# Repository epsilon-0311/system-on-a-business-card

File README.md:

# The project has been moved to [Codeberg](https://codeberg.org/epsilon-0311/system-on-a-business-card). 

# system-on-a-business-card (SoBC)

The System on a Business Card is a miniature system in the size of a business card.
It is controlled by a ESP32-C3 microncontroller which shall run Zephyr RTOS in the future.
Since this goal is to also use the PCB is a business card, the predominant factor is the size which is 55x85 mm which seems to be the standard, at least for Europe.

A interactive Bill of Materials for the latest released board revision can be found [here](KiCAD/system-on-a-business-card/bom/ibom.html).
Alternatively, if you have the repositoy open on Github, please use this [link](https://htmlpreview.github.io/?https://github.com/epsilon-0311/system-on-a-business-card/blob/main/KiCAD/system-on-a-business-card/bom/ibom.html). 

For further details on how to customize the desing to add your contact details please have a look at [Customization of the PCB](KiCAD/doc/README.md#Customization-of-the-PCB).

## Hardware Design

The system uses the on-board USB Type C recepticle for power delivery and a ESP32-C3 as its host.
As the microcontroller also supports Bluetooth and Wifi the design includes a PCB antenna as well.
One of the most prominent elements of the board is 0.77 inch OLED screen which is used to display various graphics.
Instead of using typical low profile buttons the board has resistive touch pads for the main controls.
More details on the harware design can be found [here](KiCAD/doc/README.md).

Design renderings of a revision 1.A PCB:

Finished board revision 1.A PCB:

Fully assembled revision 1.A PCB:

## Zephyr
At the moment I'm working on getting Zephyr running.
A basic hardware configuration for the board is already available inside the Zephyr directory.
It builds and a minimal example is also available.
Unfortunately, I'm still waiting on my parts to finish the boards of my first batch.

As soon as I have a functioning board configuration, the goal is to submit the board to Zephry such that is officially supported.
Further, Zephyr currently does not support the used OLED dispaly controller (SSD1312).
Therefore, an additional goal is to submit a driver to the Zephyr project.

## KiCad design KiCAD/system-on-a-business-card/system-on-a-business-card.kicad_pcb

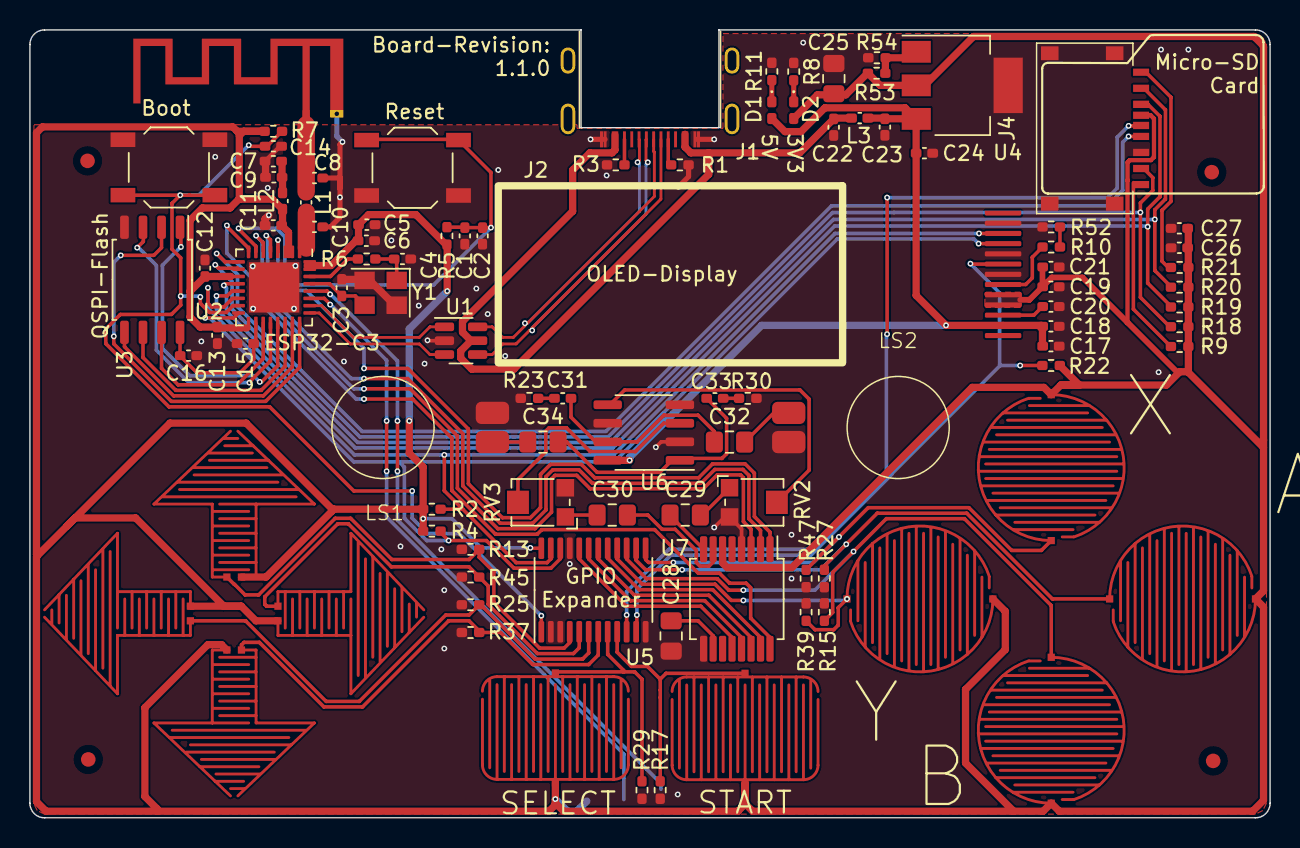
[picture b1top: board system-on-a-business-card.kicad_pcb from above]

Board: 2 copper layers, 85.0 x 54.0 mm, 103 parts (1 on the bottom side), 74 nets.

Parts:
AE1: Texas_SWRA117D_2.4GHz; Texas_SWRA117D_2.4GHz_Left
C1, C5: 1u; C_0402_1005Metric_Pad0.74x0.62mm_HandSolder
C2, C6, C9, C11, C12, C13, C14, C16, C17, C19, C22, C23, C27: 100n; C_0402_1005Metric_Pad0.74x0.62mm_HandSolder
C3, C4: 10p; C_0402_1005Metric_Pad0.74x0.62mm_HandSolder
C7, C15, C24, C26: 10u; C_0402_1005Metric_Pad0.74x0.62mm_HandSolder
C8, C10: 3p3; C_0402_1005Metric_Pad0.74x0.62mm_HandSolder
C18, C21: 4u7; C_0402_1005Metric_Pad0.74x0.62mm_HandSolder
C20: 2u2; C_0402_1005Metric_Pad0.74x0.62mm_HandSolder
C25, C28, C29, C30: 10u; C_0805_2012Metric_Pad1.18x1.45mm_HandSolder
C31, C33: 50n; C_0402_1005Metric_Pad0.74x0.62mm_HandSolder
C32, C34: 250u; C_0805_2012Metric_Pad1.18x1.45mm_HandSolder
D1, D2: XL-1005UGC; D_0402_1005Metric_Pad0.77x0.64mm_HandSolder
FID1, FID2, FID3, FID4: Fiducial; Fiducial_1mm_Mask2mm
J1: USB_C_Receptacle; USB_C_Receptacle_SHOU_HAN_TYPE_C_16P_CB1.6_073
J2: X077-6428TSWCG01-H13
J3: Conn_01x04_Socket; solder_pads_4x1
J4: TF-018B-H15; microSD_HC_Hanbo_Electronic_TF-018B-H15
L1, L2, L3: 2n2; L_0402_1005Metric_Pad0.77x0.64mm_HandSolder
LS1: Speaker_Left; Radial_10mm
LS2: Speaker_Right; Radial_10mm
R1, R2, R3, R4, R5, R7, R22: 5k1; R_0402_1005Metric_Pad0.72x0.64mm_HandSolder
R6, R53: 121R; R_0402_1005Metric_Pad0.72x0.64mm_HandSolder
R8, R9, R11, R18, R19, R20, R21: 47k; R_0402_1005Metric_Pad0.72x0.64mm_HandSolder
R10, R52: 200k; R_0402_1005Metric_Pad0.72x0.64mm_HandSolder
R12: BTN_UP; Resistive_Pad_Arrow_10mm
R13, R15, R17, R25, R27, R29, R37, R39, R45, R47: 1M; R_0402_1005Metric_Pad0.72x0.64mm_HandSolder
R14: BTN_B; Resistive_Pad_round_10_mm
R16: BTN_START; Resistive_Pad_rectangular_rounded_7x10mm
R23, R30: 10R; R_0402_1005Metric_Pad0.72x0.64mm_HandSolder
R24: BTN_LEFT; Resistive_Pad_Arrow_10mm
R26: BTN_A; Resistive_Pad_round_10_mm
R28: BTN_SELECT; Resistive_Pad_rectangular_rounded_7x10mm
R36: BTN_DOWN; Resistive_Pad_Arrow_10mm
R38: BTN_Y; Resistive_Pad_round_10_mm
R44: BTN_RIGHT; Resistive_Pad_Arrow_10mm
R46: BTN_X; Resistive_Pad_round_10_mm
R54: 75R; R_0402_1005Metric_Pad0.72x0.64mm_HandSolder
RV2, RV3: 10k; Potentiometer_Bourns_TC33X_Vertical
SW1, SW2: SW_Push; SW_SPST_TL3342
U1: USBLC6-2SC6; SOT-23-6
U2: ESP32-C3; QFN-32-1EP_5x5mm_P0.5mm_EP3.45x3.45mm
U3: ZD25WQ32C; SOP-8_5.28x5.23mm_P1.27mm
U4: ZD1117ILTRAD; SOT-223
U5: TCA9535PWR; TSSOP-24_4.4x7.8mm_P0.65mm
U6: RC4580; SOIC-8_3.9x4.9mm_P1.27mm
U7: PCM1754; SSOP-16_5.3x6.2mm_P0.65mm
Y1: 40MHz; Crystal_SMD_3225-4Pin_3.2x2.5mm

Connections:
+3.3V: C5.1, C6.1, C11.1, C12.1, C13.1, C19.1, C21.1, C25.1, C26.1, C27.1, D2.2 (A), J2.4, J2.5, J3.4, J4.4 (VDD), L2.2, R2.1, R4.1, R5.1, R7.1, R9.1, R12.2, R14.1, R16.2, R18.1, R19.1, R20.1, R21.1, R22.1, R24.2, R26.1, R28.2, R36.2, R38.1, R44.2, R46.1, R53.1, U2.2 (VDD3P3), U2.3 (VDD3P3), U2.11 (VDD3P3_RTC), U2.17 (VDD3P3_CPU), U2.31 (VDDA), U2.32 (VDDA), U4.2 (V_OUT), U5.24 (VCC), U7.6 (VCC)
+5V: C17.1, C18.1, C23.1, C24.1, D1.2 (A), J2.2, L3.2, U4.3 (V_IN), U6.8 (V+)
/Audio Circuit/BCLK: U2.4 (XTAL_32K_P/ADC1_CH0), U7.1 (BCK)
/Audio Circuit/DEMP: U5.19 (P16), U7.13 (DEMP)
/Audio Circuit/FMT: U5.17 (P14), U7.15 (FMT)
/Audio Circuit/LRCLK: U2.6 (GPIO2/ADC1_CH2), U7.3 (LRCK)
/Audio Circuit/MUTE: U5.18 (P15), U7.14 (MUTE)
/Audio Circuit/SCLK: U2.8 (GPIO3/ADC1_CH3), U7.16 (SCK)
/Audio Circuit/SERIAL_DATA: U2.5 (XTAL_32K_N/ADC1_CH1), U7.2 (DATA)
/Audio Circuit/TEST: U5.20 (P17), U7.12 (TEST)
/Display Circuit/SCL: J2.10, R4.2, U2.16 (GPIO10), U5.22 (SCL)
/Display Circuit/SDA: J2.11, R2.2, U2.14 (GPIO8), U5.23 (SDA)
/Host/MISO: J4.7 (DAT0), R18.2, U2.10 (MTDI/GPIO5/ADC2_CH0)
/Host/MOSI: J4.3 (CMD), R19.2, U2.13 (MTDO/GPIO7)
/Host/SCK: J4.5 (CLK), U2.9 (MTMS/GPIO4/ADC1_CH4)
/Host/SS: J4.2 (DAT3/CD), R20.2, U2.12 (MTCK/GPIO6)
/Power Circuit/USB_VBUS: C22.1, J1.A4 (VBUS), J1.A9 (VBUS), J1.B4 (VBUS), J1.B9 (VBUS), L3.1, U1.5 (VBUS)
/Resistive Touch Circuit/SDCard_DET: J4.9 (DET), U5.10 (P06)
A: R26.2, R27.1, U5.14 (P11)
B: R14.2, R15.1, U5.15 (P12)
BOOT: C14.1, R7.2, SW2.2, U2.15 (GPIO9/BOOT), U5.1 (~INT)
CC1: J1.A5 (CC1), R1.1
CC2: J1.B5 (CC2), R3.1
Channel_Left: C30.1, RV3.1
Channel_Right: C29.1, RV2.1
DOWN: R36.1, R37.1, U5.7 (P03)
GND: AE1.2 (GND), C1.2, C2.2, C3.1, C4.1, C5.2, C6.2, C7.2, C8.2, C9.2, C10.2, C11.2, C12.2, C13.2, C14.2, C15.2, C16.2, C17.2, C18.2, C19.2, C20.2, C21.2, C22.2, C23.2, C24.2, C25.2, C26.2, C27.2, C28.2, J1.A1 (GND), J1.A12 (GND), J1.B1 (GND), J1.B12 (GND), J2.7, J2.9, J2.12, J3.1, J4.6 (VSS), J4.10 (SHIELD), LS1.2, LS2.2, R1.2, R3.2, R8.2, R11.2, R13.2, R15.2, R17.2, R23.2, R25.2, R27.2, R29.2, R30.2, R37.2, R39.2, R45.2, R47.2, R52.1, R54.2, RV2.3, RV3.3, SW1.1, SW2.1, U1.2 (GND), U2.33 (GND), U3.4 (GND), U4.4 (GND), U5.2 (A1), U5.3 (A2), U5.12 (GND), U5.21 (A0), U6.2 (-), U6.4 (V-), U6.6 (-), U7.4 (DGND), U7.9 (AGND), Y1.2, Y1.4
LEFT: R24.1, R25.1, U5.6 (P02)
unnamed: AE1.1 (Feed), C8.1, L1.1
unnamed: C4.2, R6.1, Y1.1
unnamed: C7.1, C9.1, L2.1
unnamed: C31.1, C32.2, U6.7
unnamed: C31.2, R23.1
unnamed: C32.1, LS2.1
unnamed: C33.1, C34.2, U6.1
unnamed: C33.2, R30.1
unnamed: C34.1, LS1.1
unnamed: D1.1 (K), R11.1
unnamed: D2.1 (K), R8.1
unnamed: C20.1, J2.3
unnamed: J2.6, R10.2
unnamed: J4.8 (DAT1), R9.2
unnamed: J4.1 (DAT2), R21.2
unnamed: R10.1, R52.2
unnamed: C10.1, L1.2, U2.1 (LNA_IN)
unnamed: U2.22 (SPICLK/GPIO15), U3.6 (SCK)
unnamed: U2.21 (SPICS0/GPIO14), U3.1 (~CS)
unnamed: U2.23 (SPID/GPIO16), U3.5 (SI/IO0)
unnamed: U2.19 (SPIHD/GPIO12), U3.7 (~HOLD/IO3)
unnamed: U2.24 (SPIQ/GPIO17), U3.2 (SO/IO1)
unnamed: U2.20 (SPIWP/GPIO13), U3.3 (~WP/IO2)
unnamed: C15.1, C16.1, U2.18 (VDD_SPI/GPIO11), U3.8 (VCC)
unnamed: C3.2, U2.29 (XTAL_N), Y1.3
unnamed: R6.2, U2.30 (XTAL_P)
unnamed: R53.2, R54.1, U4.1 (VSS/ADJ)
unnamed: RV3.2, U6.3 (+)
unnamed: RV2.2, U6.5 (+)
unnamed: C28.1, U7.10 (VCOM)
unnamed: C30.2, U7.7 (VOUTL)
unnamed: C29.2, U7.8 (VOUTR)
RESET: C1.1, C2.1, R5.2, SW1.2, U2.7 (CHIP_EN)
RESET_DISPLAY: J2.8, R22.2, U5.11 (P07)
RIGHT: R44.1, R45.1, U5.5 (P01)
SELECT: R28.1, R29.1, U5.8 (P04)
START: R16.1, R17.1, U5.9 (P05)
UART_RXD: J3.3, U2.27 (U0RXD/GPIO20)
UART_TXD: J3.2, U2.28 (U0TXD/GPIO21)
UP: R12.1, R13.1, U5.4 (P00)
USB_D+: U1.1 (I/O1), U2.26 (GPIO19/USB_D+)
USB_D-: U1.3 (I/O2), U2.25 (GPIO18/USB_D-)
USB_Recepticle_D+: J1.A6 (D+), J1.B6 (D+), U1.6 (I/O1)
USB_Recepticle_D-: J1.A7 (D-), J1.B7 (D-), U1.4 (I/O2)
X: R46.2, R47.1, U5.13 (P10)
Y: R38.2, R39.1, U5.16 (P13)

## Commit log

2023-01-27 Created Board Rev 1.A
    added kicad project
    replaced gd32vf103c with rp2040
    switched to esp32-c3
    added library for touch controler, changed filename of host to host, added dcdc circuit, switched touch controler IC
    added antenna and and flash
    fixed relative pathing
2023-01-27 initial configuration for Zephyr board setup - needs work
2023-01-28 further configured devcie tree
2023-01-28 reset visible layers
2023-02-02 added environment publish github action
2023-02-02 Rename publish_dev_container.yaml to publish_dev_container.yml
2023-02-02 added workflow_dispatch to action
2023-02-02 github action, fixed tag naming
2023-02-03 updated gitignore for zephyr
2023-02-03 fixes in device tree
2023-02-03 added helper script
2023-02-03 added minimal example
2023-02-05 minor tweaks in design, added thermal relief vias
2023-02-05 added interactive BOM
2023-02-05 updated documentation, fixed bom export
2023-02-05 fixed typo in link
2023-02-05 Linked Release Package
2023-02-11 added sourcing guide
2023-02-11 minor sourcing guide extension, fixed typo
2023-03-22 fixed #12 connected OLED VDD pins to 3.3V power line
2023-03-22 fixes #11: Footprint of Flash IC corrected
2023-03-25 added adapted version of SpaceTrash from u8g2
2023-03-28 added EEPROM to store highscore
2023-03-31 fixes #15: moved wire to connecting D1 from L3 to C24
2023-03-31 resolves #13: changed resistor for LED from 121R to 47k to reduce brightness significantly
2023-03-31 Updated documentation and production files
2023-04-06 fixed EEPROM save high score bug
2023-04-06 updated latest ibom revision
2023-04-06 fixed zephyr board definition
2023-04-10 fixes #17: updates resistor values R53 and R54, updated board revision silkscreen
2023-04-15 #4: initial setup for OLED driver
2023-04-23 #4: fixed project setup to build with drivers
2023-04-23 updated development environment
2023-04-23 #4: clean up of example application repository and initial kconfig for board
2023-05-20 #4 fixed missing configuration values
2023-05-20 #4 fixed display orientation
2023-05-20 #4 clean up of drivers
2023-05-21 #4: set theme to dark mode
2023-05-21 #4: clean up of code
2023-06-10 renamed board_test to workspace
2023-06-10 renamed app to board_test
2023-06-11 #18: Initial commit for space trash
2023-08-07 fixed compilation issues
2023-08-07 added initial constructs for game
2023-08-13 added diplay label, due to zephyr chosen issue
2023-08-13 #18: started migrating bitmap assest from u8g2 to lvgl
2023-08-15 #18: updated reading of button states
2023-08-15 #18: started writing wrapper functions for graphics library
2023-08-16 #18: started working on text
2023-08-16 #18: addded further graphics helper functions
2023-08-17 #18: started working on game itself, added directional controls of space ship
2023-08-19 #18 implemented first gameplay
2023-08-23 #18: started implementation of textinput for scoreboard
2023-08-24 #18: implemented text input
2023-08-26 #18 implemented scoreboard
2023-08-26 #18: added nvm storage for scoreboard
2023-09-02 #18: tuning game mechanics, adding logs
2023-09-02 #10: added buzzer, io-expander, removed transistors from resistive pad cirucit
2023-09-02 #10: added LED for 3.3V rail
2023-09-03 #10: removed on/off switch again, started working on layout
2023-09-03 #10: updated buzzer circuit
2023-09-04 #10: continued layouting, added 2nd buzzer
2023-09-09 #10: started with routing
2023-09-13 #10: added micro sd card
2023-09-15 #10: continued with routing
2023-09-15 #10: fixed library paths
2023-09-15 #10: finished routing except PCB antenna
2023-09-15 #10: finished initial routing
2023-09-16 #10: added pull-ups to SD-Card connection, tweaks in layout
2023-09-17 #10: connected display reset to GPIO Expander
2023-09-20 #10: added missing hierachical sheet
2023-09-23 #10: mintor tweaks in routing, removed fiducials from bom, added values to buzzer and sd-card slot
2023-09-25 #10: separated reset and display reset signals, added pull-up to display reset
2023-10-21 #10: fixed wiring for display reset
2023-11-01 #10: minor tweaks
2023-11-01 #10: created version with DAC, Op Amp and speaker
